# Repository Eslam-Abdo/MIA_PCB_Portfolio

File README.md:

# M.I.A PCB Design Portfolio
This portfolio showcases the PCB designs created by the M.I.A technical team from Alexandria University. The team has participated in various robotics competitions such as MATEROV, Robocon, and Minesweeper. I have contributed to the team's designs as a member of the ABU Robocon team.

## Overview
The M.I.A team has designed and fabricated numerous PCBs for their competition robots using various tools such as Eagle PCB and Altium Designer. The team also creates 3D models of their PCB designs to visualize how they will fit in their robot.

## Projects
This portfolio includes 3D models of the following PCBs that I have designed and fabricated as part of the ABU Robocon team:

- Motor driver circuit
- Sensor interface circuit
- Microcontroller circuit
- Power supply circuit
- Communication circuit

## Preview
Below are 3D models of the PCB designs created by the M.I.A team:
 <!-- 4 pics at row -->
<!--

|  |  |  |  |
| ------- | ------- | ------- | ------- |
|  |  |  |  |
|  |  |  |  |
|  |  |  |  |
|  |  |   |  |
|  |  |  |  |
|  |  |  |  |

-->

 <!-- 3 pics at row -->
|  |  |  |
| ------- | ------- | ------- |
|  |  |  |
|  |  |  |
|  |  |  |
|  |  |  |
|  |  |   |
|  |  |  |
|  |  |  |
|  |  |  |

## Contact
If you are interested in my services for your next PCB design and fabrication project, please feel free to contact me.

Email: **eng-islam.abdo1722@alexu.edu.eg**

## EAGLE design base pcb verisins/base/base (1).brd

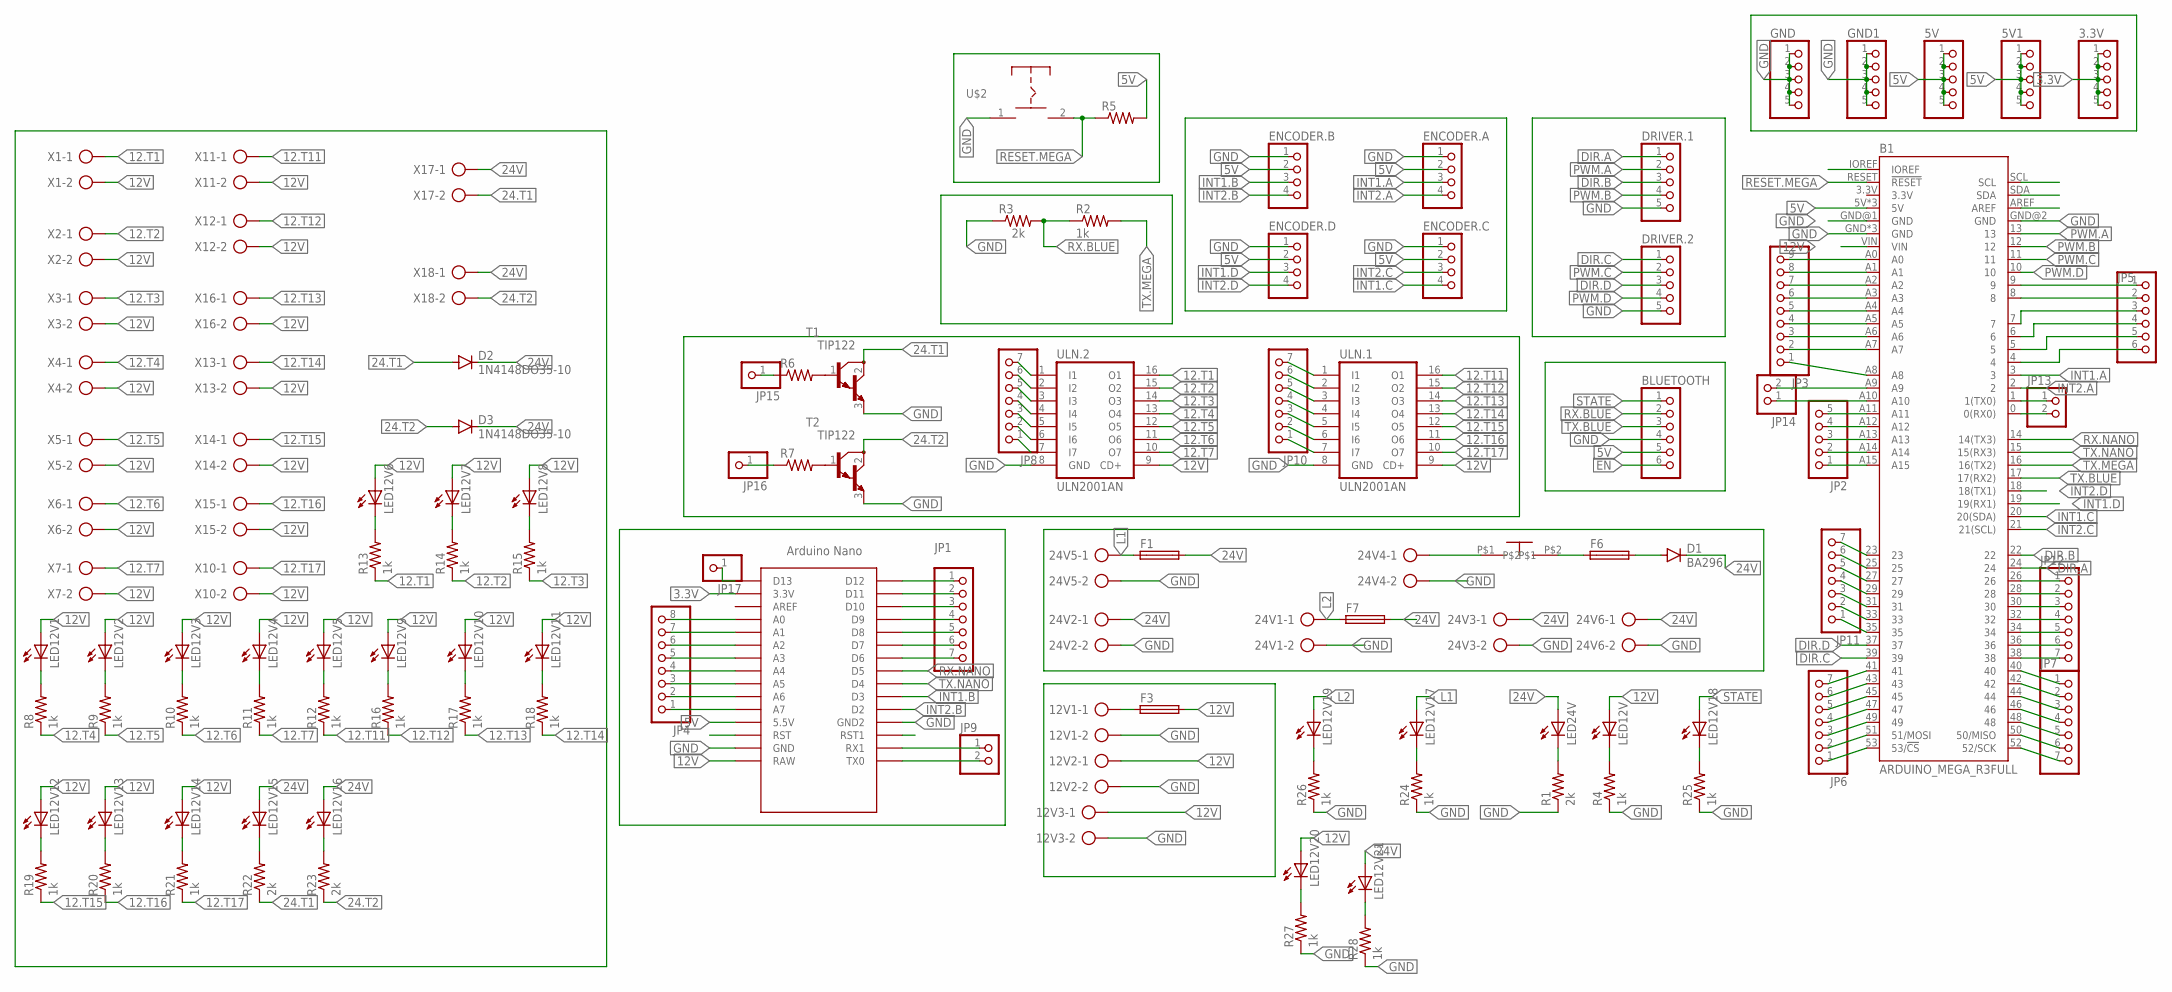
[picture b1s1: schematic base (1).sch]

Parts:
3.3V, 5V, 5V1: PINHD-1X5; 1X05
12V1, 12V2, 12V3, 24V2, 24V3, 24V6: AK300/2
24V1, 24V4, 24V5: W237-113
B1: ARDUINO_MEGA_R3FULL; ARDUINO_MEGA_NO_SILK
BLUETOOTH: PINHD-1X6; 1X06
D1: BA296; P2-15
D2, D3: 1N4148DO35-10; DO35-10
DRIVER.1, DRIVER.2: PINHD-1X5; 1X05
ENCODER.A, ENCODER.B, ENCODER.C, ENCODER.D: PINHD-1X4; 1X04
F1, F3, F6, F7: SH22,5A
GND, GND1: PINHD-1X5; 1X05
JP1, JP6, JP7, JP8, JP10, JP11, JP12: PINHD-1X7; 1X07
JP2: PINHD-1X5; 1X05
JP3: PINHD-1X9; 1X09
JP4: PINHD-1X8; 1X08
JP5: PINHD-1X6; 1X06
JP9, JP13, JP14: PINHD-1X2; 1X02
JP15, JP16, JP17: PINHD-1X1; 1X01
LED12V, LED24V: LED5MM
LED12V1, LED12V2, LED12V3, LED12V4, LED12V5, LED12V6, LED12V7, LED12V8, LED12V9, LED12V10, LED12V11, LED12V12, LED12V13, LED12V14, LED12V15, LED12V16, LED12V17, LED12V18, LED12V19, LED12V20, LED12V21: LED3MM
R1, R3, R22, R23: 2k; 0207/10
R2: 1k; 0204/7
R4, R8, R9, R10, R11, R12, R13, R14, R15, R16, R17, R18, R19, R20, R21: 1k; 0207/10
R5: R-US_0204/7; 0204/7
R6, R7: R-US_0207/10; 0207/10
R24: 1k; 0207/12
R25, R26, R27, R28: 1k; 0204/5
T1, T2: TIP122; TO220
U$1: NANO
U$2: PUSHBOTTON
U$3: ON_OFF
ULN.1, ULN.2: ULN2001AN; DIL16
X1, X2, X3, X4, X5, X6, X7, X10, X11, X12, X13, X14, X15, X16, X17, X18: AK300/2

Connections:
3.3V: 3.3V.1, 3.3V.2, 3.3V.3, 3.3V.4, 3.3V.5, U$1.3.3V
5V: 5V.1, 5V.2, 5V.3, 5V.4, 5V.5, 5V1.1, 5V1.2, 5V1.3, 5V1.4, 5V1.5, B1.5V, B1.5V@1 (5V), B1.5V@2 (5V), BLUETOOTH.5, ENCODER.A.2, ENCODER.B.2, ENCODER.C.2, ENCODER.D.2, R5.2, U$1.5V (5.5V)
12.T1: R13.1, ULN.2.16 (O1), X1.1
12.T2: R14.1, ULN.2.15 (O2), X2.1
12.T3: R15.1, ULN.2.14 (O3), X3.1
12.T4: R8.1, ULN.2.13 (O4), X4.1
12.T5: R9.1, ULN.2.12 (O5), X5.1
12.T6: R10.1, ULN.2.11 (O6), X6.1
12.T7: R11.1, ULN.2.10 (O7), X7.1
12.T11: R12.1, ULN.1.16 (O1), X11.1
12.T12: R16.1, ULN.1.15 (O2), X12.1
12.T13: R17.1, ULN.1.14 (O3), X16.1
12.T14: R18.1, ULN.1.13 (O4), X13.1
12.T15: R19.1, ULN.1.12 (O5), X14.1
12.T16: R20.1, ULN.1.11 (O6), X15.1
12.T17: R21.1, ULN.1.10 (O7), X10.1
12V: 12V2.1, 12V3.1, B1.VIN, F3.2, LED12V.A, LED12V1.A, LED12V2.A, LED12V3.A, LED12V4.A, LED12V5.A, LED12V6.A, LED12V7.A, LED12V8.A, LED12V9.A, LED12V10.A, LED12V11.A, LED12V12.A, LED12V13.A, LED12V14.A, LED12V20.A, U$1.RAW, ULN.1.9 (CD+), ULN.2.9 (CD+), X1.2, X2.2, X3.2, X4.2, X5.2, X6.2, X7.2, X10.2, X11.2, X12.2, X13.2, X14.2, X15.2, X16.2
24.T1: D2.A, R22.1, T1.2 (C), X17.2
24.T2: D3.A, R23.1, T2.2 (C), X18.2
24V: 24V2.1, 24V3.1, 24V6.1, D1.C, D2.C, D3.C, F1.2, F7.2, LED12V15.A, LED12V16.A, LED12V21.A, LED24V.A, X17.1, X18.1
40: B1.40, JP7.1
DIR.A: B1.24, DRIVER.1.1
DIR.B: B1.22, DRIVER.1.3
DIR.C: B1.39, DRIVER.2.1
DIR.D: B1.37, DRIVER.2.3
EN: BLUETOOTH.6
GND: 12V1.2, 12V2.2, 12V3.2, 24V1.2, 24V2.2, 24V3.2, 24V4.2, 24V5.2, 24V6.2, B1.GND, B1.GND@1 (GND), B1.GND@2 (GND), B1.GND@3 (GND), B1.GND@4 (GND), BLUETOOTH.4, DRIVER.1.5, DRIVER.2.5, ENCODER.A.1, ENCODER.B.1, ENCODER.C.1, ENCODER.D.1, GND.1, GND.2, GND.3, GND.4, GND.5, GND1.1, GND1.2, GND1.3, GND1.4, GND1.5, R1.1, R3.1, R4.1, R24.1, R25.1, R26.1, R27.1, R28.1, T1.3 (E), T2.3 (E), U$1.GND, U$1.GND1 (GND2), U$2.1, ULN.1.8 (GND), ULN.2.8 (GND)
INT1.A: B1.3, ENCODER.A.3
INT1.B: ENCODER.B.3, U$1.D3
INT1.C: B1.20 (20(SDA)), ENCODER.C.4
INT1.D: B1.19 (19(RX1)), ENCODER.D.3
INT2.A: B1.2, ENCODER.A.4
INT2.B: ENCODER.B.4, U$1.D2
INT2.C: B1.21 (21(SCL)), ENCODER.C.3
INT2.D: B1.18 (18(TX1)), ENCODER.D.4
L1: 24V5.1, F1.1, LED12V17.A
L2: 24V1.1, F7.1, LED12V19.A
unnamed: 24V4.1, U$3.P$1
unnamed: F6.1, U$3.P$2
unnamed: B1.9, JP5.1
unnamed: B1.8, JP5.2
unnamed: B1.7, JP5.3
unnamed: B1.6, JP5.4
unnamed: B1.5, JP5.5
unnamed: B1.4, JP5.6
unnamed: JP8.1, ULN.2.7 (I7)
unnamed: LED12V1.K (C), R8.2
unnamed: B1.1 (1(TX0)), JP13.1
unnamed: B1.0 (0(RX0)), JP13.2
unnamed: LED12V18.K (C), R25.2
unnamed: LED12V19.K (C), R26.2
unnamed: LED24V.K (C), R1.2
unnamed: LED12V.K (C), R4.2
unnamed: D1.A, F6.2
unnamed: LED12V2.K (C), R9.2
unnamed: LED12V3.K (C), R10.2
unnamed: LED12V4.K (C), R11.2
unnamed: LED12V5.K (C), R12.2
unnamed: LED12V6.K (C), R13.2
unnamed: LED12V7.K (C), R14.2
unnamed: LED12V8.K (C), R15.2
unnamed: LED12V9.K (C), R16.2
unnamed: LED12V10.K (C), R17.2
unnamed: B1.42, JP7.2
unnamed: B1.44, JP7.3
unnamed: B1.46, JP7.4
unnamed: B1.48, JP7.5
unnamed: B1.50 (50/MISO), JP7.6
unnamed: B1.52 (52/SCK), JP7.7
unnamed: LED12V11.K (C), R18.2
unnamed: LED12V12.K (C), R19.2
unnamed: B1.A15, JP2.1
unnamed: B1.A14, JP2.2
unnamed: B1.A13, JP2.3
unnamed: B1.A0, JP3.9
unnamed: B1.A1, JP3.8
unnamed: B1.A2, JP3.7
unnamed: B1.A3, JP3.6
unnamed: B1.A4, JP3.5
unnamed: B1.A5, JP3.4
unnamed: B1.A6, JP3.3
unnamed: B1.A7, JP3.2
unnamed: B1.A8, JP3.1
unnamed: B1.A12, JP2.4
unnamed: B1.A11, JP2.5
unnamed: LED12V13.K (C), R20.2
unnamed: LED12V14.K (C), R21.2
unnamed: LED12V15.K (C), R22.2
unnamed: LED12V16.K (C), R23.2
unnamed: LED12V17.K (C), R24.2
unnamed: JP8.2, ULN.2.6 (I6)
unnamed: JP8.3, ULN.2.5 (I5)
unnamed: JP8.4, ULN.2.4 (I4)
unnamed: JP8.5, ULN.2.3 (I3)
unnamed: JP8.6, ULN.2.2 (I2)
unnamed: JP8.7, ULN.2.1 (I1)
unnamed: JP10.1, ULN.1.7 (I7)
unnamed: JP10.2, ULN.1.6 (I6)
unnamed: JP10.3, ULN.1.5 (I5)
unnamed: B1.41, JP6.7
unnamed: B1.45, JP6.5
unnamed: B1.43, JP6.6
unnamed: B1.47, JP6.4
unnamed: B1.49, JP6.3
unnamed: B1.51 (51/MOSI), JP6.2
unnamed: B1.53 (53/!CS), JP6.1
unnamed: JP10.4, ULN.1.4 (I4)
unnamed: JP10.5, ULN.1.3 (I3)
unnamed: JP10.6, ULN.1.2 (I2)
unnamed: JP10.7, ULN.1.1 (I1)
unnamed: B1.35, JP11.1
unnamed: B1.33, JP11.2
unnamed: B1.31, JP11.3
unnamed: B1.29, JP11.4
unnamed: B1.27, JP11.5
unnamed: B1.25, JP11.6
unnamed: B1.23, JP11.7
unnamed: B1.26, JP12.1
unnamed: B1.28, JP12.2
unnamed: B1.30, JP12.3
unnamed: B1.32, JP12.4
unnamed: R6.2, T1.1 (B)
unnamed: R7.2, T2.1 (B)
unnamed: B1.34, JP12.5
unnamed: B1.36, JP12.6
unnamed: JP17.1, U$1.D13
unnamed: B1.38, JP12.7
unnamed: B1.A9, JP14.2
unnamed: JP4.8, U$1.A0
unnamed: JP4.7, U$1.A1
unnamed: JP4.6, U$1.A2
unnamed: JP4.5, U$1.A3
unnamed: JP4.4, U$1.A4
unnamed: JP4.3, U$1.A5
unnamed: JP4.2, U$1.A6
unnamed: JP4.1, U$1.A7
unnamed: B1.A10, JP14.1
unnamed: JP15.1, R6.1
unnamed: JP16.1, R7.1
unnamed: JP1.1, U$1.D12
unnamed: JP1.2, U$1.D11
unnamed: JP1.3, U$1.D10
unnamed: JP1.4, U$1.D9
unnamed: JP1.5, U$1.D8
unnamed: JP1.6, U$1.D7
unnamed: JP1.7, U$1.D6
unnamed: LED12V20.K (C), R27.2
unnamed: LED12V21.K (C), R28.2
unnamed: JP9.1, U$1.RX1
unnamed: JP9.2, U$1.TX0
unnamed: 12V1.1, F3.1
PWM.A: B1.13, DRIVER.1.2
PWM.B: B1.12, DRIVER.1.4
PWM.C: B1.11, DRIVER.2.2
PWM.D: B1.10, DRIVER.2.4
RESET.MEGA: B1.RESET (!RESET), R5.1, U$2.2
RX.BLUE: BLUETOOTH.2, R2.1, R3.2
RX.NANO: B1.14 (14(TX3)), U$1.D5
STATE: BLUETOOTH.1, LED12V18.A
TX.BLUE: B1.17 (17(RX2)), BLUETOOTH.3
TX.MEGA: B1.16 (16(TX2)), R2.2
TX.NANO: B1.15 (15(RX3)), U$1.D4

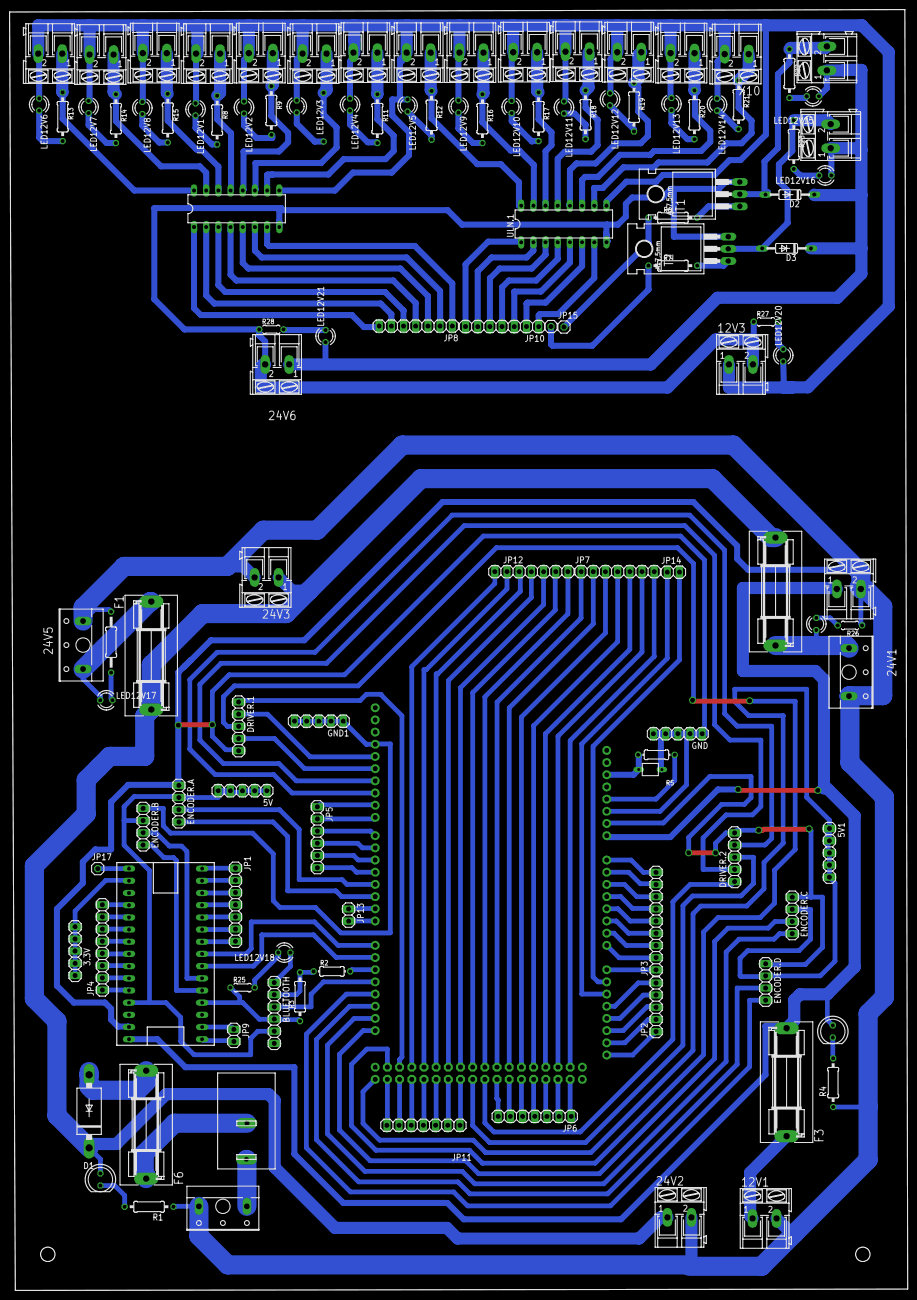
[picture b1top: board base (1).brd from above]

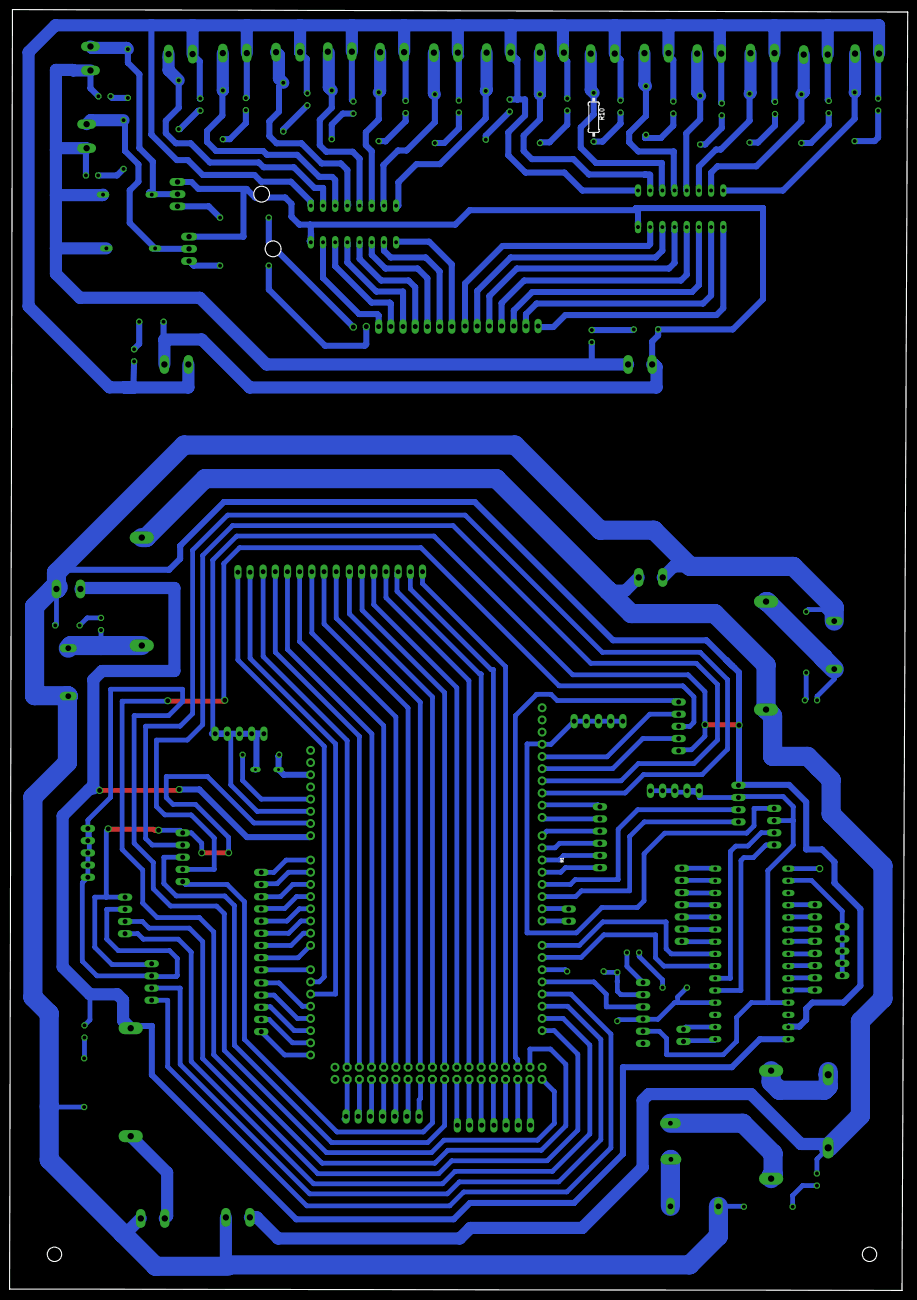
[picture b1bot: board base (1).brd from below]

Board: 2 copper layers, 187.2 x 267.0 mm, 120 parts (2 on the bottom side), 161 nets.

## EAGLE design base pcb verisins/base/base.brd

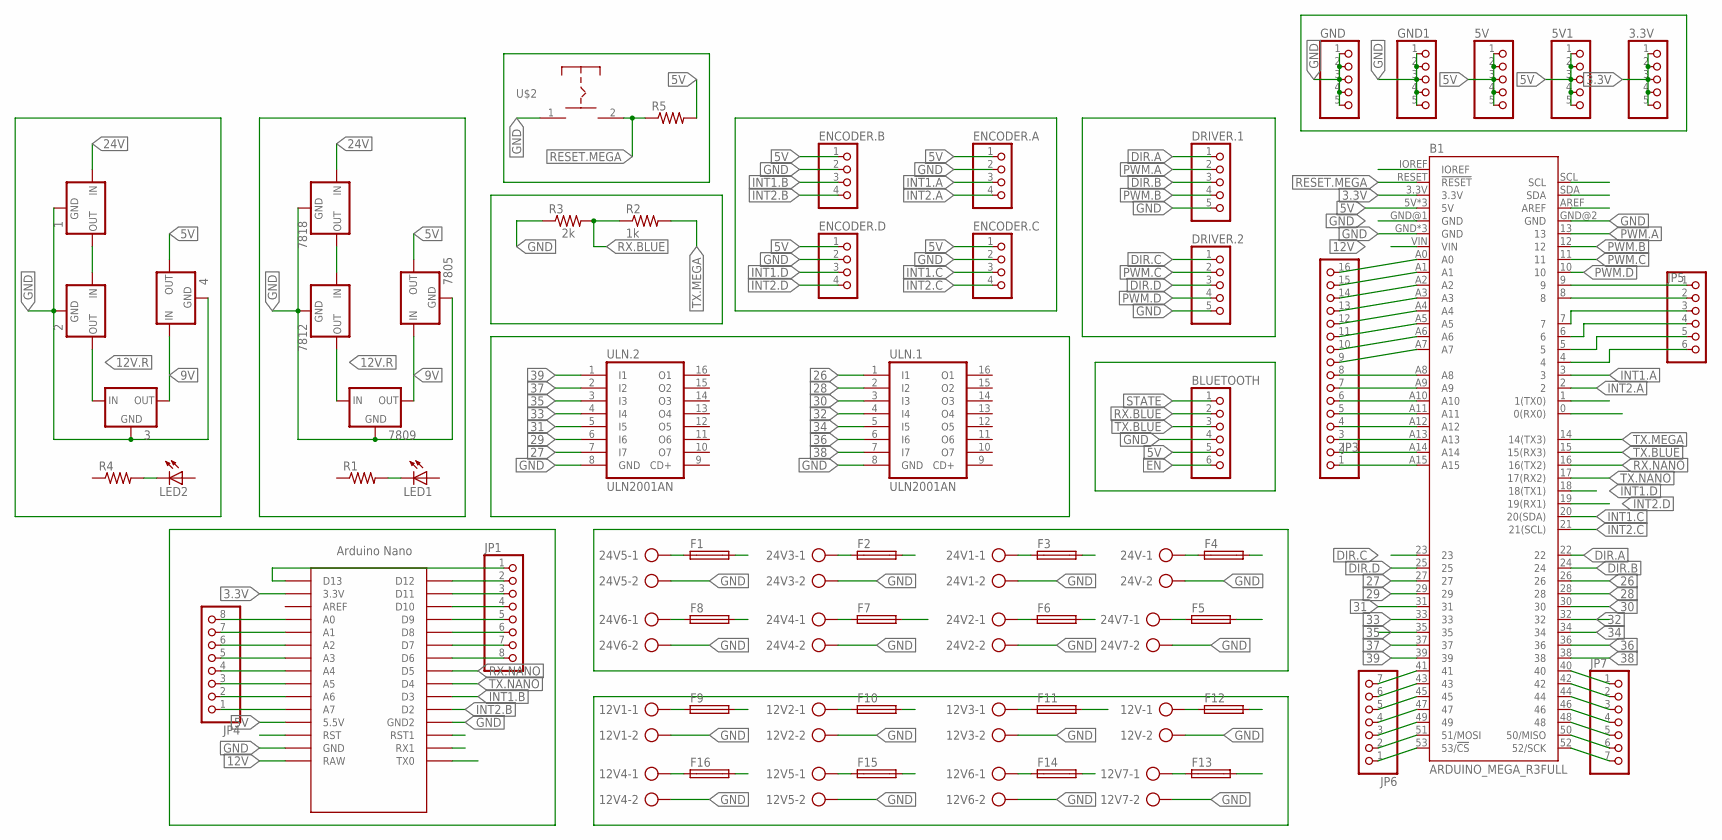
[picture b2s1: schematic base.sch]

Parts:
1, 2, 3, 4, 7805, 7809, 7812, 7818: 78XXS
3.3V, 5V, 5V1: PINHD-1X5; 1X05
12V, 12V1, 12V2, 12V3, 12V4, 12V5, 12V6, 12V7, 24V, 24V1, 24V2, 24V3, 24V4, 24V5, 24V6, 24V7: AK300/2
B1: ARDUINO_MEGA_R3FULL; ARDUINO_MEGA_NO_SILK
BLUETOOTH: PINHD-1X6; 1X06
DRIVER.1, DRIVER.2: PINHD-1X5; 1X05
ENCODER.A, ENCODER.B, ENCODER.C, ENCODER.D: PINHD-1X4; 1X04
F1, F2, F3, F4, F5, F6, F7, F8, F9, F10, F11, F12, F13, F14, F15, F16: GSH15
GND, GND1: PINHD-1X5; 1X05
JP1, JP4: PINHD-1X8; 1X08
JP3: PINHD-1X16; 1X16
JP5: PINHD-1X6; 1X06
JP6, JP7: PINHD-1X7; 1X07
LED1, LED2: LED5MM
R1, R4, R5: R-US_0204/7; 0204/7
R2: 1k; 0204/7
R3: 2k; 0207/10
U$1: NANO
U$2: PUSHBOTTON
ULN.1, ULN.2: ULN2001AN; DIL16

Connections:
3.3V: 3.3V.1, 3.3V.2, 3.3V.3, 3.3V.4, 3.3V.5, B1.3.3V, U$1.3.3V
5V: 4.OUT, 5V.1, 5V.2, 5V.3, 5V.4, 5V.5, 5V1.1, 5V1.2, 5V1.3, 5V1.4, 5V1.5, 7805.OUT, B1.5V, B1.5V@1 (5V), B1.5V@2 (5V), BLUETOOTH.5, ENCODER.A.1, ENCODER.B.1, ENCODER.C.1, ENCODER.D.1, R5.2, U$1.5V (5.5V)
9V: 3.OUT, 4.IN, 7805.IN, 7809.OUT
12V: B1.VIN, U$1.RAW
12V.R: 2.OUT, 3.IN, 7809.IN, 7812.OUT
24V: 1.IN, 7818.IN
26: B1.26, ULN.1.1 (I1)
27: B1.27, ULN.2.7 (I7)
28: B1.28, ULN.1.2 (I2)
29: B1.29, ULN.2.6 (I6)
30: B1.30, ULN.1.3 (I3)
31: B1.31, ULN.2.5 (I5)
32: B1.32, ULN.1.4 (I4)
33: B1.33, ULN.2.4 (I4)
34: B1.34, ULN.1.5 (I5)
35: B1.35, ULN.2.3 (I3)
36: B1.36, ULN.1.6 (I6)
37: B1.37, ULN.2.2 (I2)
38: B1.38, ULN.1.7 (I7)
39: B1.39, ULN.2.1 (I1)
40: B1.40, JP7.1
DIR.A: B1.22, DRIVER.1.1
DIR.B: B1.24, DRIVER.1.3
DIR.C: B1.23, DRIVER.2.1
DIR.D: B1.25, DRIVER.2.3
EN: BLUETOOTH.6
GND: 1.GND, 2.GND, 3.GND, 4.GND, 12V.2, 12V1.2, 12V2.2, 12V3.2, 12V4.2, 12V5.2, 12V6.2, 12V7.2, 24V.2, 24V1.2, 24V2.2, 24V3.2, 24V4.2, 24V5.2, 24V6.2, 24V7.2, 7805.GND, 7809.GND, 7812.GND, 7818.GND, B1.GND, B1.GND@1 (GND), B1.GND@2 (GND), B1.GND@3 (GND), B1.GND@4 (GND), BLUETOOTH.4, DRIVER.1.5, DRIVER.2.5, ENCODER.A.2, ENCODER.B.2, ENCODER.C.2, ENCODER.D.2, GND.1, GND.2, GND.3, GND.4, GND.5, GND1.1, GND1.2, GND1.3, GND1.4, GND1.5, R3.1, U$1.GND, U$1.GND1 (GND2), U$2.1, ULN.1.8 (GND), ULN.2.8 (GND)
INT1.A: B1.3, ENCODER.A.3
INT1.B: ENCODER.B.3, U$1.D3
INT1.C: B1.20 (20(SDA)), ENCODER.C.3
INT1.D: B1.18 (18(TX1)), ENCODER.D.3
INT2.A: B1.2, ENCODER.A.4
INT2.B: ENCODER.B.4, U$1.D2
INT2.C: B1.21 (21(SCL)), ENCODER.C.4
INT2.D: B1.19 (19(RX1)), ENCODER.D.4
unnamed: 7812.IN, 7818.OUT
unnamed: LED2.K (C), R4.2
unnamed: B1.9, JP5.1
unnamed: B1.8, JP5.2
unnamed: B1.7, JP5.3
unnamed: B1.6, JP5.4
unnamed: B1.5, JP5.5
unnamed: B1.4, JP5.6
unnamed: 1.OUT, 2.IN
unnamed: B1.42, JP7.2
unnamed: B1.44, JP7.3
unnamed: B1.46, JP7.4
unnamed: B1.48, JP7.5
unnamed: B1.50 (50/MISO), JP7.6
unnamed: B1.52 (52/SCK), JP7.7
unnamed: B1.A0, JP3.16
unnamed: B1.A1, JP3.15
unnamed: B1.A2, JP3.14
unnamed: B1.A3, JP3.13
unnamed: B1.A4, JP3.12
unnamed: B1.A5, JP3.11
unnamed: B1.A6, JP3.10
unnamed: B1.A7, JP3.9
unnamed: B1.A8, JP3.8
unnamed: B1.A9, JP3.7
unnamed: B1.A10, JP3.6
unnamed: B1.A11, JP3.5
unnamed: B1.A12, JP3.4
unnamed: B1.A13, JP3.3
unnamed: B1.A14, JP3.2
unnamed: B1.A15, JP3.1
unnamed: B1.41, JP6.7
unnamed: B1.45, JP6.5
unnamed: B1.43, JP6.6
unnamed: B1.47, JP6.4
unnamed: B1.49, JP6.3
unnamed: B1.51 (51/MOSI), JP6.2
unnamed: B1.53 (53/!CS), JP6.1
unnamed: LED1.K (C), R1.2
unnamed: JP1.1, U$1.D13
unnamed: JP4.8, U$1.A0
unnamed: JP4.7, U$1.A1
unnamed: JP4.6, U$1.A2
unnamed: JP4.5, U$1.A3
unnamed: JP4.4, U$1.A4
unnamed: JP4.3, U$1.A5
unnamed: JP4.2, U$1.A6
unnamed: JP4.1, U$1.A7
unnamed: JP1.2, U$1.D12
unnamed: JP1.3, U$1.D11
unnamed: JP1.4, U$1.D10
unnamed: JP1.5, U$1.D9
unnamed: JP1.6, U$1.D8
unnamed: JP1.7, U$1.D7
unnamed: JP1.8, U$1.D6
unnamed: 12V7.1, F13.1
unnamed: 24V5.1, F1.1
unnamed: 24V6.1, F8.1
unnamed: 24V3.1, F2.1
unnamed: 24V4.1, F7.1
unnamed: 24V1.1, F3.1
unnamed: 24V.1, F4.1
unnamed: 24V7.1, F5.1
unnamed: 24V2.1, F6.1
unnamed: 12V2.1, F10.1
unnamed: 12V3.1, F11.1
unnamed: 12V.1, F12.1
unnamed: 12V6.1, F14.1
unnamed: 12V5.1, F15.1
unnamed: 12V4.1, F16.1
unnamed: 12V1.1, F9.1
PWM.A: B1.13, DRIVER.1.2
PWM.B: B1.12, DRIVER.1.4
PWM.C: B1.11, DRIVER.2.2
PWM.D: B1.10, DRIVER.2.4
RESET.MEGA: B1.RESET (!RESET), R5.1, U$2.2
RX.BLUE: BLUETOOTH.2, R2.1, R3.2
RX.NANO: B1.16 (16(TX2)), U$1.D5
STATE: BLUETOOTH.1
TX.BLUE: B1.15 (15(RX3)), BLUETOOTH.3
TX.MEGA: B1.14 (14(TX3)), R2.2
TX.NANO: B1.17 (17(RX2)), U$1.D4

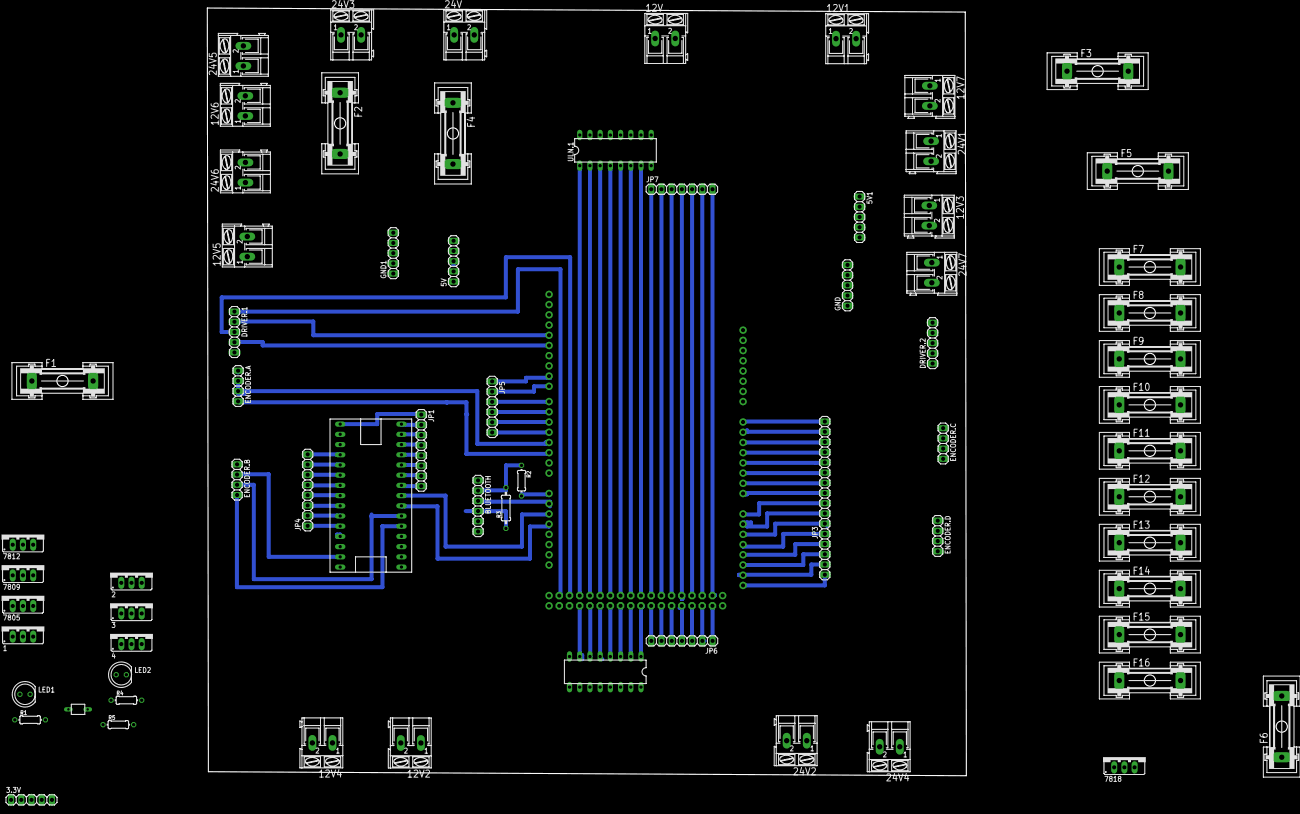
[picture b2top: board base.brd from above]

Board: 2 copper layers, 188.8 x 191.0 mm, 70 parts (1 on the bottom side), 115 nets.

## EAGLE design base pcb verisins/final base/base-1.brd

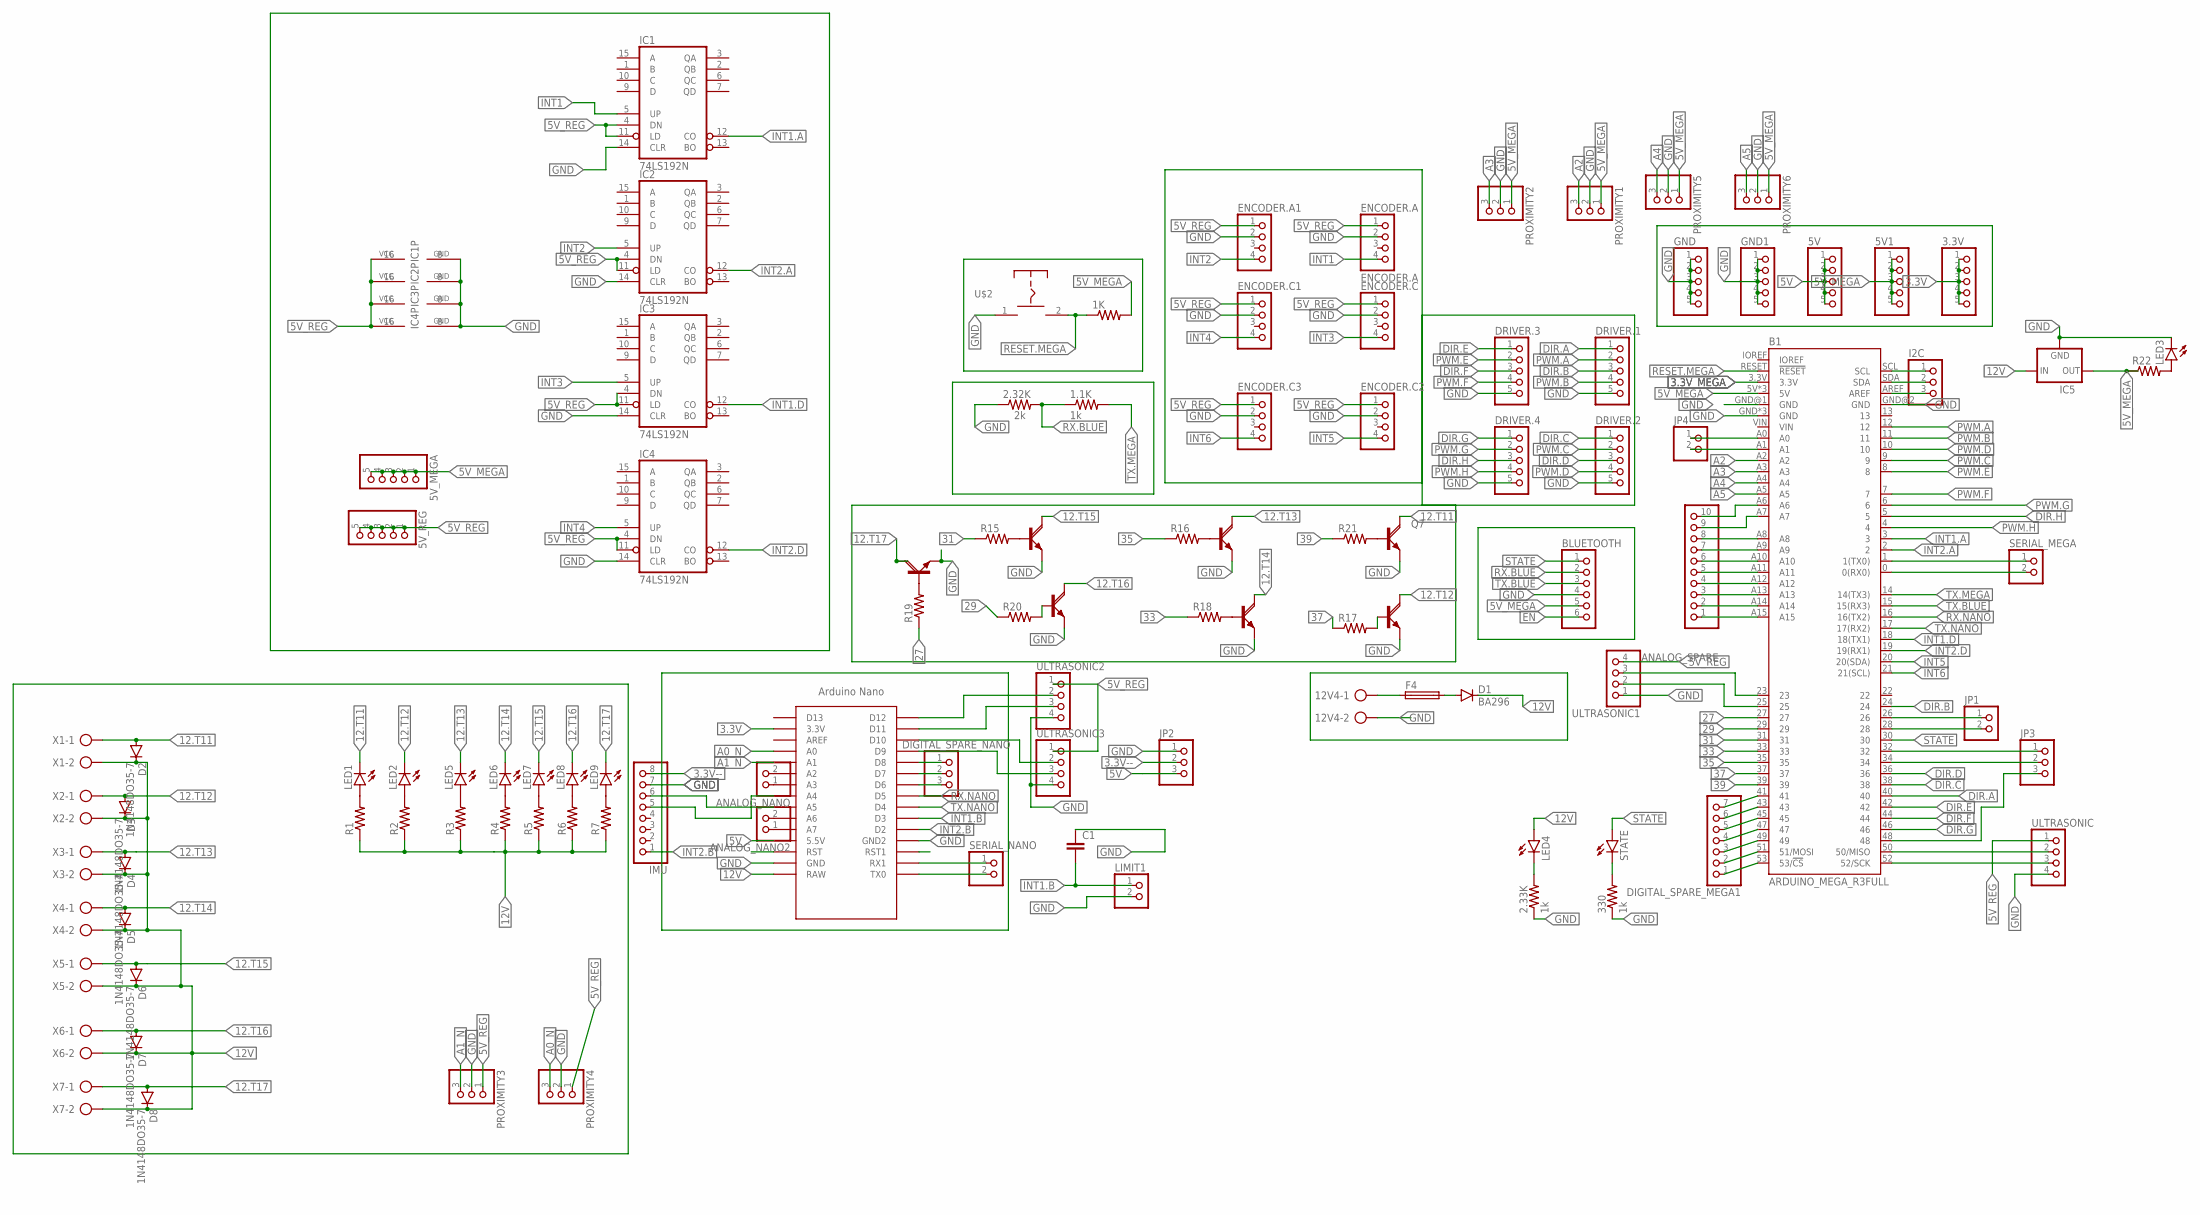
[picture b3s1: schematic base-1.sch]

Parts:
1.1K, 330: 1k; 0204/5
1K: R-US_0204/5; 0204/5
2.32K: 2k; 0204/5
2.33K: 1k; 0207/10
3.3V, 5V, 5V1, 5V_MEGA, 5V_REG: PINHD-1X5; 1X05
12V4: W237-113
ANALOG_NANO, ANALOG_NANO2: PINHD-1X2; 1X02
ANALOG_SPARE: PINHD-1X10; 1X10
B1: ARDUINO_MEGA_R3FULL; ARDUINO_MEGA_NO_SILK
BLUETOOTH: PINHD-1X6; 1X06
C1: C-EU025-025X050; C025-025X050
D1: BA296; P2-15
D2, D3, D4, D5, D6, D7, D8: 1N4148DO35-7; DO35-7
DIGITAL_SPARE_MEGA1: PINHD-1X7; 1X07
DIGITAL_SPARE_NANO: PINHD-1X3; 1X03
DRIVER.1, DRIVER.2, DRIVER.3, DRIVER.4: PINHD-1X5; 1X05
ENCODER.A: ENCODER.A; 1X04
ENCODER.A1, ENCODER.C, ENCODER.C1, ENCODER.C2, ENCODER.C3: PINHD-1X4; 1X04
F4: SH22,5A
GND, GND1: PINHD-1X5; 1X05
I2C: PINHD-1X3; 1X03
IC1, IC2, IC3, IC4: 74LS192N; DIL16
IC5: 79XX-TO3; TO3-79
IMU: PINHD-1X8; 1X08
JP1, JP4: PINHD-1X2; 1X02
JP2, JP3: PINHD-1X3; 1X03
LED1, LED2, LED3, LED5, LED6, LED7, LED8, LED9: LED3MM
LED4: LED5MM
LIMIT1: PINHD-1X2; 1X02
PROXIMITY1, PROXIMITY2, PROXIMITY3, PROXIMITY4, PROXIMITY5, PROXIMITY6: PINHD-1X3; 1X03
Q1, Q2, Q3, Q4, Q5, Q6, Q7: TIP120; TO220AV
R1, R2, R3, R4, R5, R6, R7, R21, R22: R-US_0204/5; 0204/5
R15: R-US_0207/10; 0207/10
R16, R17, R18, R19, R20: R-US_0204/7; 0204/7
SERIAL_MEGA: PINHD-1X2; 1X02
SERIAL_NANO: PINHD-1X2; 1X02
STATE: LED3MM
U$1: NANO
U$2: PUSHBOTTON
ULTRASONIC, ULTRASONIC1, ULTRASONIC2, ULTRASONIC3: PINHD-1X4; 1X04
X1, X2, X3, X4, X5, X6, X7: AK300/2

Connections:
3.3V: 3.3V.1, 3.3V.2, 3.3V.3, 3.3V.4, 3.3V.5, U$1.3.3V
3.3V--: IMU.8, JP2.2
3.3V_MEGA: B1.3.3V
5V: 5V.1, 5V.2, 5V.3, 5V.4, 5V.5, JP2.3, U$1.5V (5.5V)
5V_MEGA: 1K.2, 5V1.1, 5V1.2, 5V1.3, 5V1.4, 5V1.5, 5V_MEGA.1, 5V_MEGA.2, 5V_MEGA.3, 5V_MEGA.4, 5V_MEGA.5, B1.5V, B1.5V@1 (5V), B1.5V@2 (5V), BLUETOOTH.5, IC5.1 (OUT), PROXIMITY1.1, PROXIMITY2.1, PROXIMITY5.1, PROXIMITY6.1, R22.1
5V_REG: 5V_REG.1, 5V_REG.2, 5V_REG.3, 5V_REG.4, 5V_REG.5, ENCODER.A.1, ENCODER.A1.1, ENCODER.C.1, ENCODER.C1.1, ENCODER.C2.1, ENCODER.C3.1, IC1.4 (DN), IC1.11 (LD), IC1.16 (VCC), IC2.4 (DN), IC2.11 (LD), IC2.16 (VCC), IC3.4 (DN), IC3.11 (LD), IC3.16 (VCC), IC4.4 (DN), IC4.11 (LD), IC4.16 (VCC), PROXIMITY3.1, PROXIMITY4.1, ULTRASONIC.1, ULTRASONIC1.4, ULTRASONIC2.1, ULTRASONIC3.1
12.T11: D2.A, LED1.K (C), Q7.C, X1.1
12.T12: D3.A, LED2.K (C), Q5.C, X2.1
12.T13: D4.A, LED5.K (C), Q2.C, X3.1
12.T14: D5.A, LED6.K (C), Q4.C, X4.1
12.T15: D6.A, LED7.K (C), Q1.C, X5.1
12.T16: D7.A, LED8.K (C), Q6.C, X6.1
12.T17: D8.A, LED9.K (C), Q3.C, X7.1
12V: D1.C, D2.C, D3.C, D4.C, D5.C, D6.C, D7.C, D8.C, IC5.3 (IN), LED4.A, R1.1, R2.1, R3.1, R4.1, R5.1, R6.1, R7.1, U$1.RAW, X1.2, X2.2, X3.2, X4.2, X5.2, X6.2, X7.2
27: B1.27, R19.1
29: B1.29, R20.1
31: B1.31, R15.1
33: B1.33, R18.1
35: B1.35, R16.1
37: B1.37, R17.1
39: B1.39, R21.1
48: B1.48, JP3.3
A0_N: PROXIMITY4.3, U$1.A0
A1_N: PROXIMITY3.3, U$1.A1
A2: B1.A2, PROXIMITY1.3
A3: B1.A3, PROXIMITY2.3
A4: B1.A4, PROXIMITY5.3
A5: B1.A5, PROXIMITY6.3
DIR.A: B1.40, DRIVER.1.1
DIR.B: B1.24, DRIVER.1.3
DIR.C: B1.38, DRIVER.2.1
DIR.D: B1.36, DRIVER.2.3
DIR.E: B1.42, DRIVER.3.1
DIR.F: B1.44, DRIVER.3.3
DIR.G: B1.46, DRIVER.4.1
DIR.H: B1.5, DRIVER.4.3
EN: BLUETOOTH.6
GND: 2.32K.1, 2.33K.1, 12V4.2, 330.1, B1.GND, B1.GND@1 (GND), B1.GND@2 (GND), B1.GND@3 (GND), B1.GND@4 (GND), BLUETOOTH.4, C1.1, DRIVER.1.5, DRIVER.2.5, DRIVER.3.5, DRIVER.4.5, ENCODER.A.2, ENCODER.A1.2, ENCODER.C.2, ENCODER.C1.2, ENCODER.C2.2, ENCODER.C3.2, GND.1, GND.2, GND.3, GND.4, GND.5, GND1.1, GND1.2, GND1.3, GND1.4, GND1.5, IC1.8 (GND), IC1.14 (CLR), IC2.8 (GND), IC2.14 (CLR), IC3.8 (GND), IC3.14 (CLR), IC4.8 (GND), IC4.14 (CLR), IC5.2 (GND), IMU.7, JP2.1, LED3.K (C), LIMIT1.2, PROXIMITY1.2, PROXIMITY2.2, PROXIMITY3.2, PROXIMITY4.2, PROXIMITY5.2, PROXIMITY6.2, Q1.E, Q2.E, Q3.E, Q4.E, Q5.E, Q6.E, Q7.E, U$1.GND, U$1.GND1 (GND2), U$2.1, ULTRASONIC.4, ULTRASONIC1.1, ULTRASONIC2.4, ULTRASONIC3.4
INT1: ENCODER.A.4, IC1.5 (UP)
INT1.A: B1.3, IC1.12 (CO)
INT1.B: C1.2, LIMIT1.1, U$1.D3
INT1.D: B1.18 (18(TX1)), IC3.12 (CO)
INT2: ENCODER.A1.4, IC2.5 (UP)
INT2.A: B1.2, IC2.12 (CO)
INT2.B: IMU.1, U$1.D2
INT2.D: B1.19 (19(RX1)), IC4.12 (CO)
INT3: ENCODER.C.4, IC3.5 (UP)
INT4: ENCODER.C1.4, IC4.5 (UP)
INT5: B1.20 (20(SDA)), ENCODER.C2.4
INT6: B1.21 (21(SCL)), ENCODER.C3.4
unnamed: B1.SCL, I2C.1
unnamed: B1.SDA, I2C.2
unnamed: B1.AREF, I2C.3
unnamed: ANALOG_SPARE.1, B1.A15
unnamed: 12V4.1, F4.1
unnamed: ANALOG_SPARE.2, B1.A14
unnamed: ANALOG_SPARE.3, B1.A13
unnamed: ANALOG_SPARE.4, B1.A12
unnamed: ANALOG_SPARE.5, B1.A11
unnamed: ANALOG_SPARE.6, B1.A10
unnamed: ANALOG_SPARE.7, B1.A9
unnamed: ANALOG_SPARE.8, B1.A8
unnamed: ANALOG_SPARE.9, B1.A7
unnamed: LED3.A, R22.2
unnamed: B1.1 (1(TX0)), SERIAL_MEGA.1
unnamed: B1.0 (0(RX0)), SERIAL_MEGA.2
unnamed: 330.2, STATE.K (C)
unnamed: Q5.B, R17.2
unnamed: 2.33K.2, LED4.K (C)
unnamed: D1.A, F4.2
unnamed: Q6.B, R20.2
unnamed: LED1.A, R1.2
unnamed: LED2.A, R2.2
unnamed: LED5.A, R3.2
unnamed: LED6.A, R4.2
unnamed: LED7.A, R5.2
unnamed: LED8.A, R6.2
unnamed: LED9.A, R7.2
unnamed: B1.23, ULTRASONIC1.3
unnamed: B1.25, ULTRASONIC1.2
unnamed: IMU.6, U$1.A5
unnamed: IMU.5, U$1.A4
unnamed: ANALOG_NANO.1, U$1.A3
unnamed: ANALOG_NANO.2, U$1.A2
unnamed: B1.50 (50/MISO), ULTRASONIC.2
unnamed: B1.52 (52/SCK), ULTRASONIC.3
unnamed: ANALOG_NANO2.1, U$1.A7
unnamed: ANALOG_NANO2.2, U$1.A6
unnamed: B1.A0, JP4.1
unnamed: B1.26, JP1.1
unnamed: ANALOG_SPARE.10, B1.A6
unnamed: B1.A1, JP4.2
unnamed: B1.28, JP1.2
unnamed: B1.32, JP3.1
unnamed: B1.34, JP3.2
unnamed: Q1.B, R15.2
unnamed: Q2.B, R16.2
unnamed: Q4.B, R18.2
unnamed: Q3.B, R19.2
unnamed: Q7.B, R21.2
unnamed: B1.41, DIGITAL_SPARE_MEGA1.7
unnamed: B1.45, DIGITAL_SPARE_MEGA1.5
unnamed: B1.43, DIGITAL_SPARE_MEGA1.6
unnamed: B1.47, DIGITAL_SPARE_MEGA1.4
unnamed: B1.49, DIGITAL_SPARE_MEGA1.3
unnamed: B1.51 (51/MOSI), DIGITAL_SPARE_MEGA1.2
unnamed: B1.53 (53/!CS), DIGITAL_SPARE_MEGA1.1
unnamed: U$1.D12, ULTRASONIC2.2
unnamed: U$1.D11, ULTRASONIC2.3
unnamed: U$1.D10, ULTRASONIC3.2
unnamed: U$1.D9, ULTRASONIC3.3
unnamed: DIGITAL_SPARE_NANO.1, U$1.D8
unnamed: DIGITAL_SPARE_NANO.2, U$1.D7
unnamed: DIGITAL_SPARE_NANO.3, U$1.D6
unnamed: SERIAL_NANO.1, U$1.RX1
unnamed: SERIAL_NANO.2, U$1.TX0
PWM.A: B1.12, DRIVER.1.2
PWM.B: B1.11, DRIVER.1.4
PWM.C: B1.9, DRIVER.2.2
PWM.D: B1.10, DRIVER.2.4
PWM.E: B1.8, DRIVER.3.2
PWM.F: B1.7, DRIVER.3.4
PWM.G: B1.6, DRIVER.4.2
PWM.H: B1.4, DRIVER.4.4
RESET.MEGA: 1K.1, B1.RESET (!RESET), U$2.2
RX.BLUE: 1.1K.1, 2.32K.2, BLUETOOTH.2
RX.NANO: B1.16 (16(TX2)), U$1.D5
STATE: B1.30, BLUETOOTH.1, STATE.A
TX.BLUE: B1.15 (15(RX3)), BLUETOOTH.3
TX.MEGA: 1.1K.2, B1.14 (14(TX3))
TX.NANO: B1.17 (17(RX2)), U$1.D4

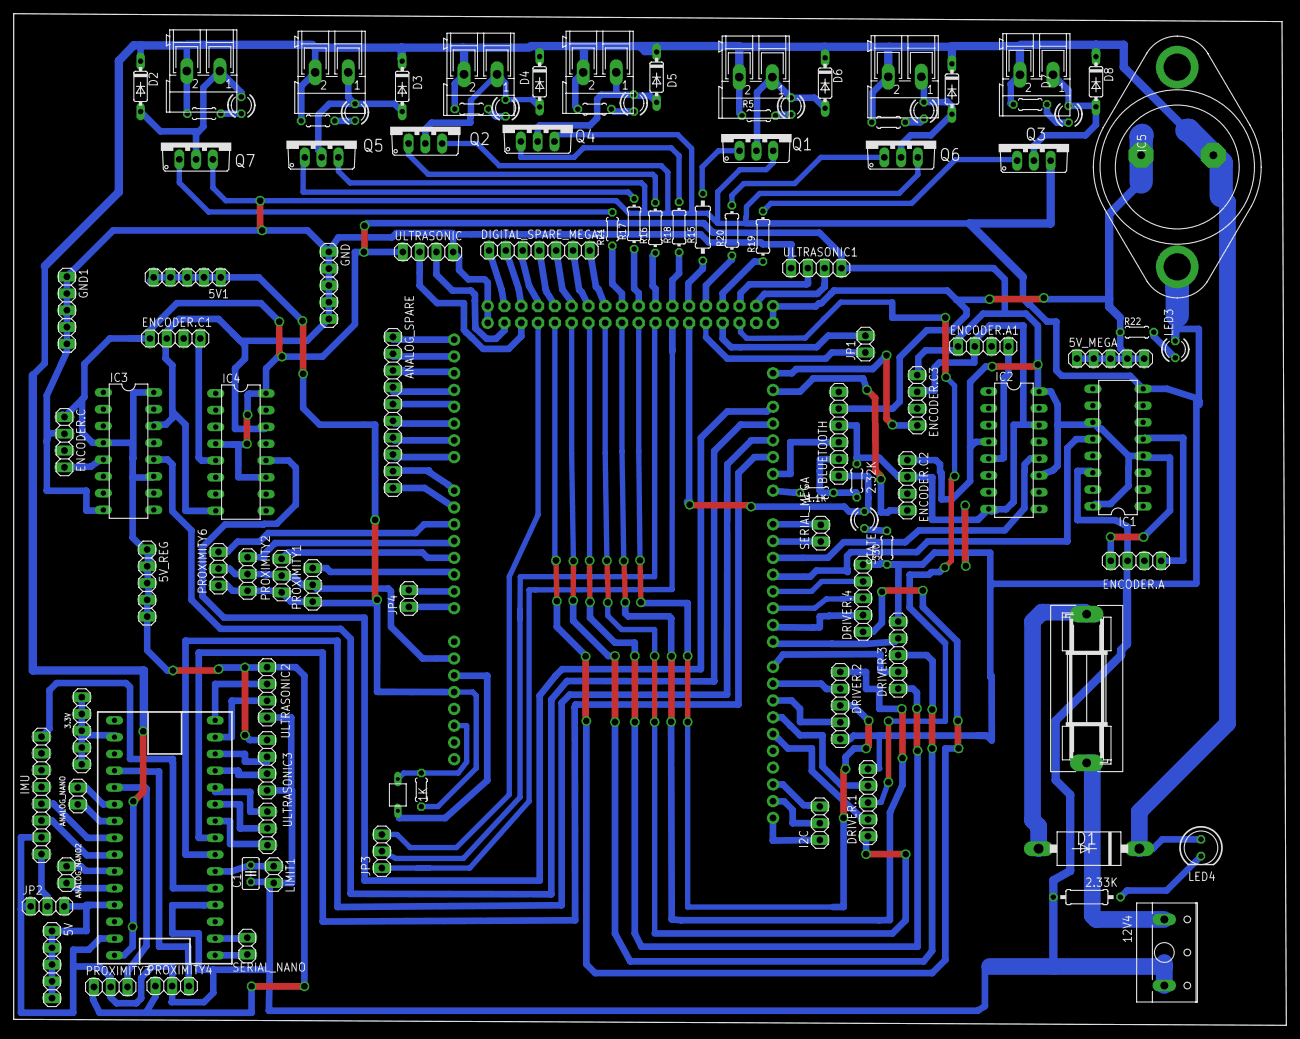
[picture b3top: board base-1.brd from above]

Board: 2 copper layers, 192.6 x 153.1 mm, 105 parts (1 on the bottom side), 129 nets.

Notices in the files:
parts and their libraries:
SparkFun-Boards: Licensing: Creative Commons ShareAlike 4.0 International - https://creativecommons.org/licenses/by-sa/4.0
